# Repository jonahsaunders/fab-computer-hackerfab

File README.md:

# FAB Computer · HackerFab

A reusable power and control backplane with plug-in boards for HackerFab tools.

[Backplane](#backplane) · [Motion controller](#motion-controller) · [Encoder splitter](#encoder-splitter) · [Sputtering cards](#sputtering-cards) · [Plug-in assembly](#plug-in-assembly)

[Manufacturing guide, JLCPCB files, and part alternatives](docs/manufacturing/README.md)

## Boards

### Backplane

[Full-size board render](docs/images/backplane.png) · [L3 inductor close-up](docs/images/backplane-regulator.png)

*KiCad 3D render of the November 10 backplane layout with revised 12 V and 5 V buck regulator placement.*

### Motion controller

### Encoder splitter

### Sputtering cards

[Card details and renders](daughterboards/sputtering/README.md) · [Card validation](daughterboards/sputtering/docs/validation.md)

## Plug-in assembly

*KiCad render with the motion controller in J1 and the encoder splitter in J2.* [Reverse view](daughterboards/micromanipulator/docs/host-adjacent-back.png)

*KiCad render with the pump, gauge and USB card in J1 and the Alicat card in J2.* [Reverse view](daughterboards/sputtering/docs/host-adjacent-back.png)

## Design files

| Board | Purpose | Open in KiCad 10 |
| --- | --- | --- |
| Backplane | RP2350B host, three DIN96 slots, shared power and buses | [Project](hardware/backplane/HackerfabBackplane.kicad_pro) · [Schematics](docs/schematics/README.md) |
| Motion controller | Bare RP2350B; XYZ motion, rotation, heater, vacuum and USB-C; 100 × 60 mm | [Project](daughterboards/micromanipulator/hardware/daughterboard/FabNanoDaughterboard.kicad_pro) · [Schematic](daughterboards/micromanipulator/docs/schematic-review.pdf) |
| Encoder splitter | Existing backplane SPI0 to three original PH6 sensor interfaces; 100 × 26 mm | [Project](daughterboards/micromanipulator/hardware/encoder-backplane/EncoderBackplane.kicad_pro) · [Schematic](daughterboards/micromanipulator/docs/encoder-backplane-schematic.pdf) |
| Sputtering pump + gauge + USB | Pump, gauge and impedance-matcher USB; 100 × 65 mm | [Project](daughterboards/sputtering/hardware/pump-gauge-usb/sputtering-pump-gauge-usb.kicad_pro) · [Schematic](daughterboards/sputtering/docs/sputtering-pump-gauge-usb-schematic.pdf) |
| Sputtering Alicat | Two Alicat flow controllers; 100 × 85 mm | [Project](daughterboards/sputtering/hardware/alicat/sputtering-alicat.kicad_pro) · [Schematic](daughterboards/sputtering/docs/sputtering-alicat-schematic.pdf) |

Clone the entire repository and keep the local libraries together. The motion and encoder cards are four-layer designs with no development modules. The sputtering cards are two-layer designs controlled by the host.

Use host **J1 or J2 for motion**, and another slot for the splitter. **The motion controller owns SPI0; host GPIO16–21 must remain inputs with no pulls.** Other cards must leave SPI0 undriven. See the [bus map and firmware requirements](daughterboards/micromanipulator/docs/backplane-encoder-bus.md).

The motion and encoder cards pass ERC, DRC, connectivity and schematic parity. Physical fit, actual load/thermal measurements, encoder signal integrity and firmware integration remain open. The backplane has its [separate validation record](docs/validation.md). All 5 V loads share the host's **2.5 A power-mux limit**; see [load limits](daughterboards/micromanipulator/docs/load-power-review.md).

[Card details and renders](daughterboards/micromanipulator/README.md) · [Card validation](daughterboards/micromanipulator/docs/validation.md) · [Architecture](docs/architecture.md) · [Connector pinout](docs/connector-pinout.md) · [Contributing](CONTRIBUTING.md)

Backplane sources: **Jonah Saunders**. Project background: **Jonah Saunders and Jacob Rohozen**. [Source history](docs/provenance.md) and [upstream licenses](daughterboards/micromanipulator/licenses/) are retained; no overall project license has been specified.

## Enclosure

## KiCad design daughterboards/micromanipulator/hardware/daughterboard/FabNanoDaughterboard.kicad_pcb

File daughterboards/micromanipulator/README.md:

# Micromanipulator cards

Bare-component adaptation of [MicroManipulatorStepper](https://github.com/hacker-fab/MicroManipulatorStepper) for the FAB Computer backplane. One RP2350B controls XYZ motion, rotation, heater and vacuum. A second, shallow card distributes encoder SPI to the three existing sensor boards. No development boards are used.

| Board | Size | Open in KiCad 10 | Review |
| --- | --- | --- | --- |
| Motion controller | 100 × 60 mm, 4 layers | [Project](hardware/daughterboard/FabNanoDaughterboard.kicad_pro) | [Schematic](docs/schematic-review.pdf), [3D](docs/board-3d.png), [BOM](docs/bom.csv) |
| Encoder splitter | 100 × 26 mm, 4 layers | [Project](hardware/encoder-backplane/EncoderBackplane.kicad_pro) | [Schematic](docs/encoder-backplane-schematic.pdf), [3D](docs/encoder-backplane.png), [BOM](docs/encoder-backplane-bom.csv) |

Keep this folder together: footprints and models resolve locally or through embedded data, with original library names preserved. Standard KiCad symbol libraries are needed for editing. Both boards use **signal / power / ground / signal**, SMD capacitors, edge-accessible connectors, and 0.8 mm bare 5 V/3.3 V probes with nearby grounds. The motion board has 117 fitted components plus four probe pads; the splitter has 11 plus four. Some models are explicitly nominal; see the [model inventory](docs/model-inventory.csv).

## Installation and bus ownership

Place motion in host **J1 or J2**; J3 lacks UART. The encoder card can use any remaining slot. SPI travels through the existing backplane contacts. **Motion owns SPI0; the host must leave GPIO16–21 as inputs with no pulls.** All three SPI0 selects are reserved for these encoders. Other cards must leave this bus undriven. The backplane design is unchanged; no 3.3 V contact was added. Local regulators derive 3.3 V from the existing 5 V rail.

The three PH6 sensor ports preserve their original pin order. The old PH8 cable connection is replaced by the DIN bus; motion GPIO44/45/46 now select the sensors. Rotation encoder J12 remains unchanged. See the [bus/contact map](docs/backplane-encoder-bus.md), [connector table](docs/connectors.csv) and [firmware integration notes](firmware/README.md). The [original 36 × 36 mm splitter](hardware/encoder-splitter/) is retained only as a source reference.

## Review status

Both active boards pass native ERC, DRC, connectivity and schematic parity; all nine schematic pages pass the geometric text/wire audit. The 35 checked direct decoupling paths and all 48 local capacitor ground returns on the motion card remain intact. USB routing now uses two signal vias per connector-to-MCU path (five physical data vias across the reversible branches) with a local ground reference beneath its connector/ESD launch; see the [USB review](docs/usb-routing-review.md). See [validation](docs/validation.md), [routing](docs/layout-front.svg), [power plane](docs/power-plane.svg), [decoupling](docs/decoupling-review.md), and [reverse assembly view](docs/host-adjacent-back.png).

These are development designs. The assembly uses nominal mating-model placement; physical seating, plugs and cable access need verification. Begin encoder SPI at 1 MHz and validate the actual harness before using the original 8 MHz rate. Firmware consolidation is outstanding; configuration headers are included, not binaries.

The host 5 V mux has a **shared 2.5 A limit**. Heater, pump, sensors, host and logic must fit within that total with margin. The source heater estimates 1.4 A; rotation/pump currents remain unspecified in the checked upstream repository. See [load limits](docs/load-power-review.md), [logic supply](docs/power-budget.md), [connector fit](docs/connector-review.md) and [sources/licenses](licenses/). No fabrication release is claimed.

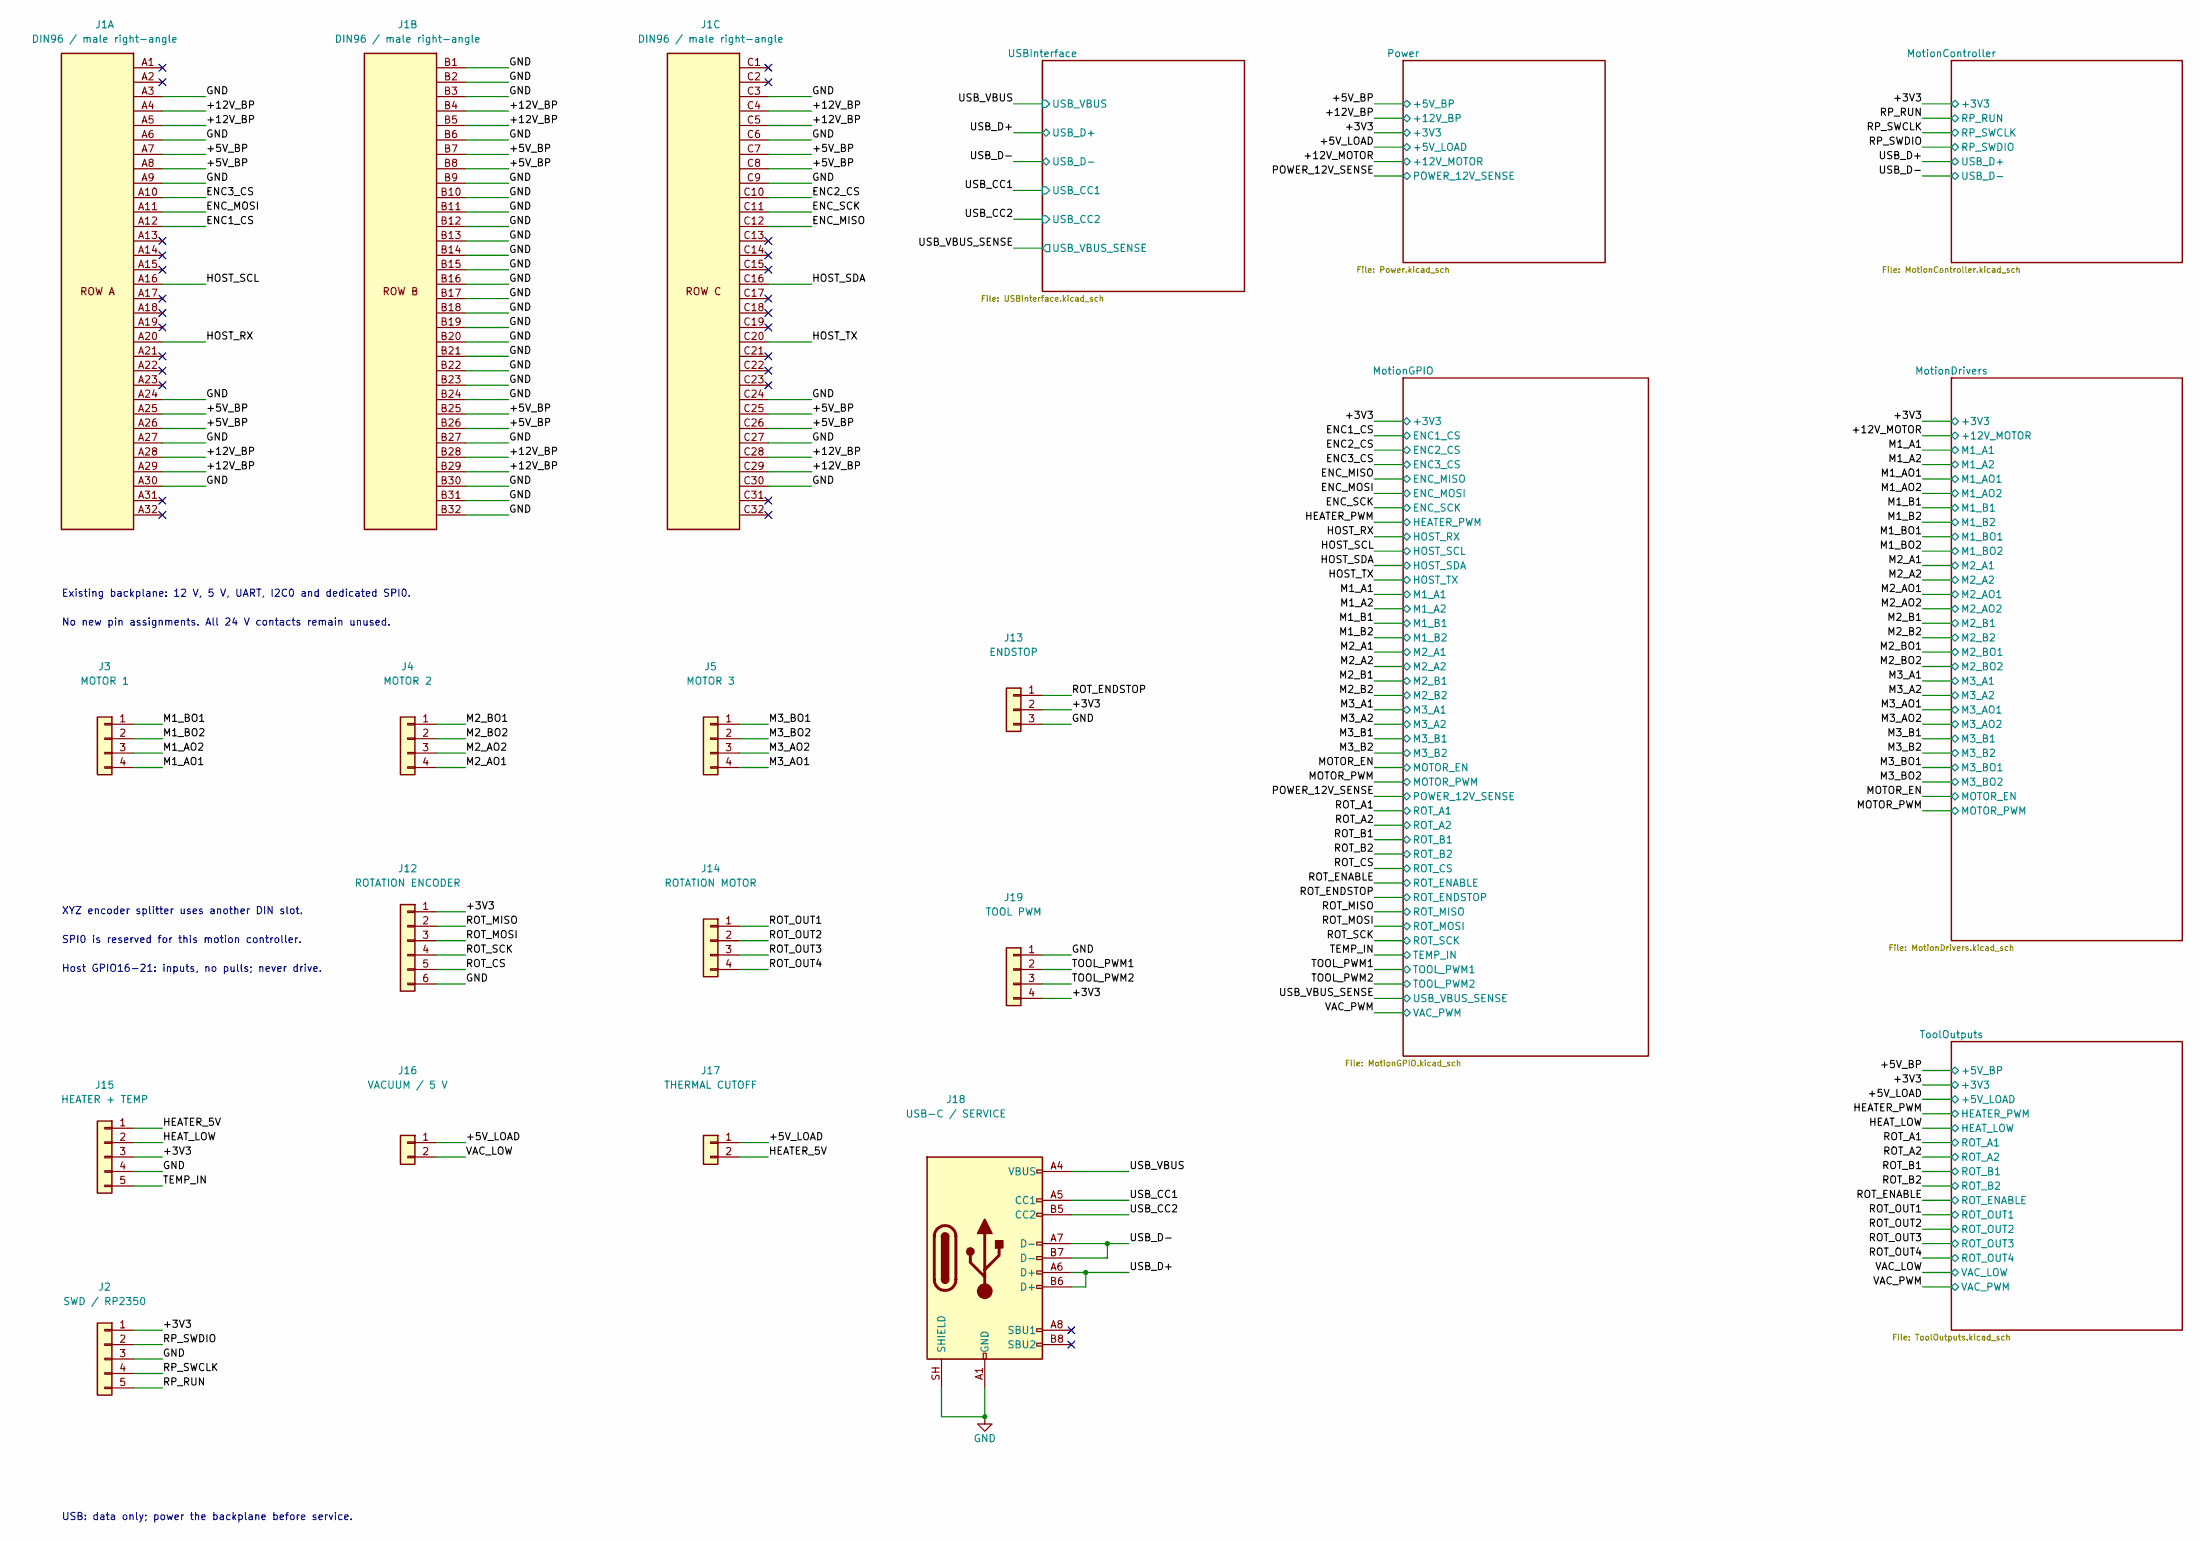
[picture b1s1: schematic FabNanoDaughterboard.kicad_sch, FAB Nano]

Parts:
J1: DIN96 / male right-angle; DIN96_Male_Horizontal; MPN 9001-11961C00A; LCSC C5173361
J2: SWD / RP2350; PinHeader_1x05_P1.27mm_Vertical; MPN PH1.27-01-05PZD; LCSC C41360740
J3: MOTOR 1; JST_PH_B4B-PH-K_1x04_P2.00mm_Vertical; MPN B4B-PH-K-S(LF)(SN); LCSC C131334
J4: MOTOR 2; JST_PH_B4B-PH-K_1x04_P2.00mm_Vertical; MPN B4B-PH-K-S(LF)(SN); LCSC C131334
J5: MOTOR 3; JST_PH_B4B-PH-K_1x04_P2.00mm_Vertical; MPN B4B-PH-K-S(LF)(SN); LCSC C131334
J12: ROTATION ENCODER; PinHeader_1x06_P2.54mm_Vertical; MPN 2.54-1x6PStraight pin; LCSC C37208
J13: ENDSTOP; JST_PH_B3B-PH-K_1x03_P2.00mm_Vertical; MPN B3B-PH-K-S(LF)(SN); LCSC C131339
J14: ROTATION MOTOR; JST_PH_B4B-PH-K_1x04_P2.00mm_Vertical; MPN B4B-PH-K-S(LF)(SN); LCSC C131334
J15: HEATER + TEMP; JST_PH_B5B-PH-K_1x05_P2.00mm_Vertical; MPN B5B-PH-K-S(LF)(SN); LCSC C157993
J16: VACUUM / 5 V; JST_PH_B2B-PH-K_1x02_P2.00mm_Vertical; MPN B2B-PH-K-S(LF)(SN); LCSC C131337
J17: THERMAL CUTOFF; JST_PH_B2B-PH-K_1x02_P2.00mm_Vertical; MPN B2B-PH-K-S(LF)(SN); LCSC C131337
J18: USB-C / SERVICE; USB_C_Receptacle_HRO_TYPE-C-31-M-12; MPN TYPE-C-31-M-12; LCSC C165948
J19: TOOL PWM; PinHeader_1x04_P1.27mm_Vertical; MPN PH1.27-01-04PZD; LCSC C41360739

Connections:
+3V3: J2.1, J12.1, J13.2, J15.3, J19.4; also elsewhere on the board
+5V_BP: J1.A7, J1.A8, J1.A25, J1.A26, J1.B7, J1.B8, J1.B25, J1.B26, J1.C7, J1.C8, J1.C25, J1.C26; also elsewhere on the board
+5V_LOAD: J16.1, J17.1; also elsewhere on the board
+12V_BP: J1.A4, J1.A5, J1.A28, J1.A29, J1.B4, J1.B5, J1.B28, J1.B29, J1.C4, J1.C5, J1.C28, J1.C29; also elsewhere on the board
/ENC1_CS: J1.A12; also elsewhere on the board
/ENC2_CS: J1.C10; also elsewhere on the board
/ENC3_CS: J1.A10; also elsewhere on the board
/ENC_MISO: J1.C12; also elsewhere on the board
/ENC_MOSI: J1.A11; also elsewhere on the board
/ENC_SCK: J1.C11; also elsewhere on the board
/HEATER_5V: J15.1, J17.2
/HEAT_LOW: J15.2; also elsewhere on the board
/HOST_RX: J1.A20; also elsewhere on the board
/HOST_SCL: J1.A16; also elsewhere on the board
/HOST_SDA: J1.C16; also elsewhere on the board
/HOST_TX: J1.C20; also elsewhere on the board
/M1_AO1: J3.4; also elsewhere on the board
/M1_AO2: J3.3; also elsewhere on the board
/M1_BO1: J3.1; also elsewhere on the board
/M1_BO2: J3.2; also elsewhere on the board
/M2_AO1: J4.4; also elsewhere on the board
/M2_AO2: J4.3; also elsewhere on the board
/M2_BO1: J4.1; also elsewhere on the board
/M2_BO2: J4.2; also elsewhere on the board
/M3_AO1: J5.4; also elsewhere on the board
/M3_AO2: J5.3; also elsewhere on the board
/M3_BO1: J5.1; also elsewhere on the board
/M3_BO2: J5.2; also elsewhere on the board
/ROT_CS: J12.5; also elsewhere on the board
/ROT_ENDSTOP: J13.1; also elsewhere on the board
/ROT_MISO: J12.2; also elsewhere on the board
/ROT_MOSI: J12.3; also elsewhere on the board
/ROT_OUT1: J14.1; also elsewhere on the board
/ROT_OUT2: J14.2; also elsewhere on the board
/ROT_OUT3: J14.3; also elsewhere on the board
/ROT_OUT4: J14.4; also elsewhere on the board
/ROT_SCK: J12.4; also elsewhere on the board
/RP_RUN: J2.5; also elsewhere on the board
/RP_SWCLK: J2.4; also elsewhere on the board
/RP_SWDIO: J2.2; also elsewhere on the board
/TEMP_IN: J15.5; also elsewhere on the board
/TOOL_PWM1: J19.2; also elsewhere on the board
/TOOL_PWM2: J19.3; also elsewhere on the board
/USB_CC1: J18.A5 (CC1); also elsewhere on the board
/USB_CC2: J18.B5 (CC2); also elsewhere on the board
/USB_D+: J18.A6 (D+), J18.B6 (D+); also elsewhere on the board
/USB_D-: J18.A7 (D-), J18.B7 (D-); also elsewhere on the board
/USB_VBUS: J18.A4 (VBUS), J18.A9 (VBUS), J18.B4 (VBUS), J18.B9 (VBUS); also elsewhere on the board
/VAC_LOW: J16.2; also elsewhere on the board
GND: J1.A3, J1.A6, J1.A9, J1.A24, J1.A27, J1.A30, J1.B1, J1.B2, J1.B3, J1.B6, J1.B9, J1.B10, J1.B11, J1.B12, J1.B13, J1.B14, J1.B15, J1.B16, J1.B17, J1.B18, J1.B19, J1.B20, J1.B21, J1.B22, J1.B23, J1.B24, J1.B27, J1.B30, J1.B31, J1.B32, J1.C3, J1.C6, J1.C9, J1.C24, J1.C27, J1.C30, J2.3, J12.6, J13.3, J15.4, J18.A1 (GND), J18.A12 (GND), J18.B1 (GND), J18.B12 (GND), J18.SH (SHIELD), J19.1; also elsewhere on the board

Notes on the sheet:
Existing backplane: 12 V, 5 V, UART, I2C0 and dedicated SPI0.
No new pin assignments. All 24 V contacts remain unused.
USB: data only; power the backplane before service.
XYZ encoder splitter uses another DIN slot.
SPI0 is reserved for this motion controller.
Host GPIO16-21: inputs, no pulls; never drive.

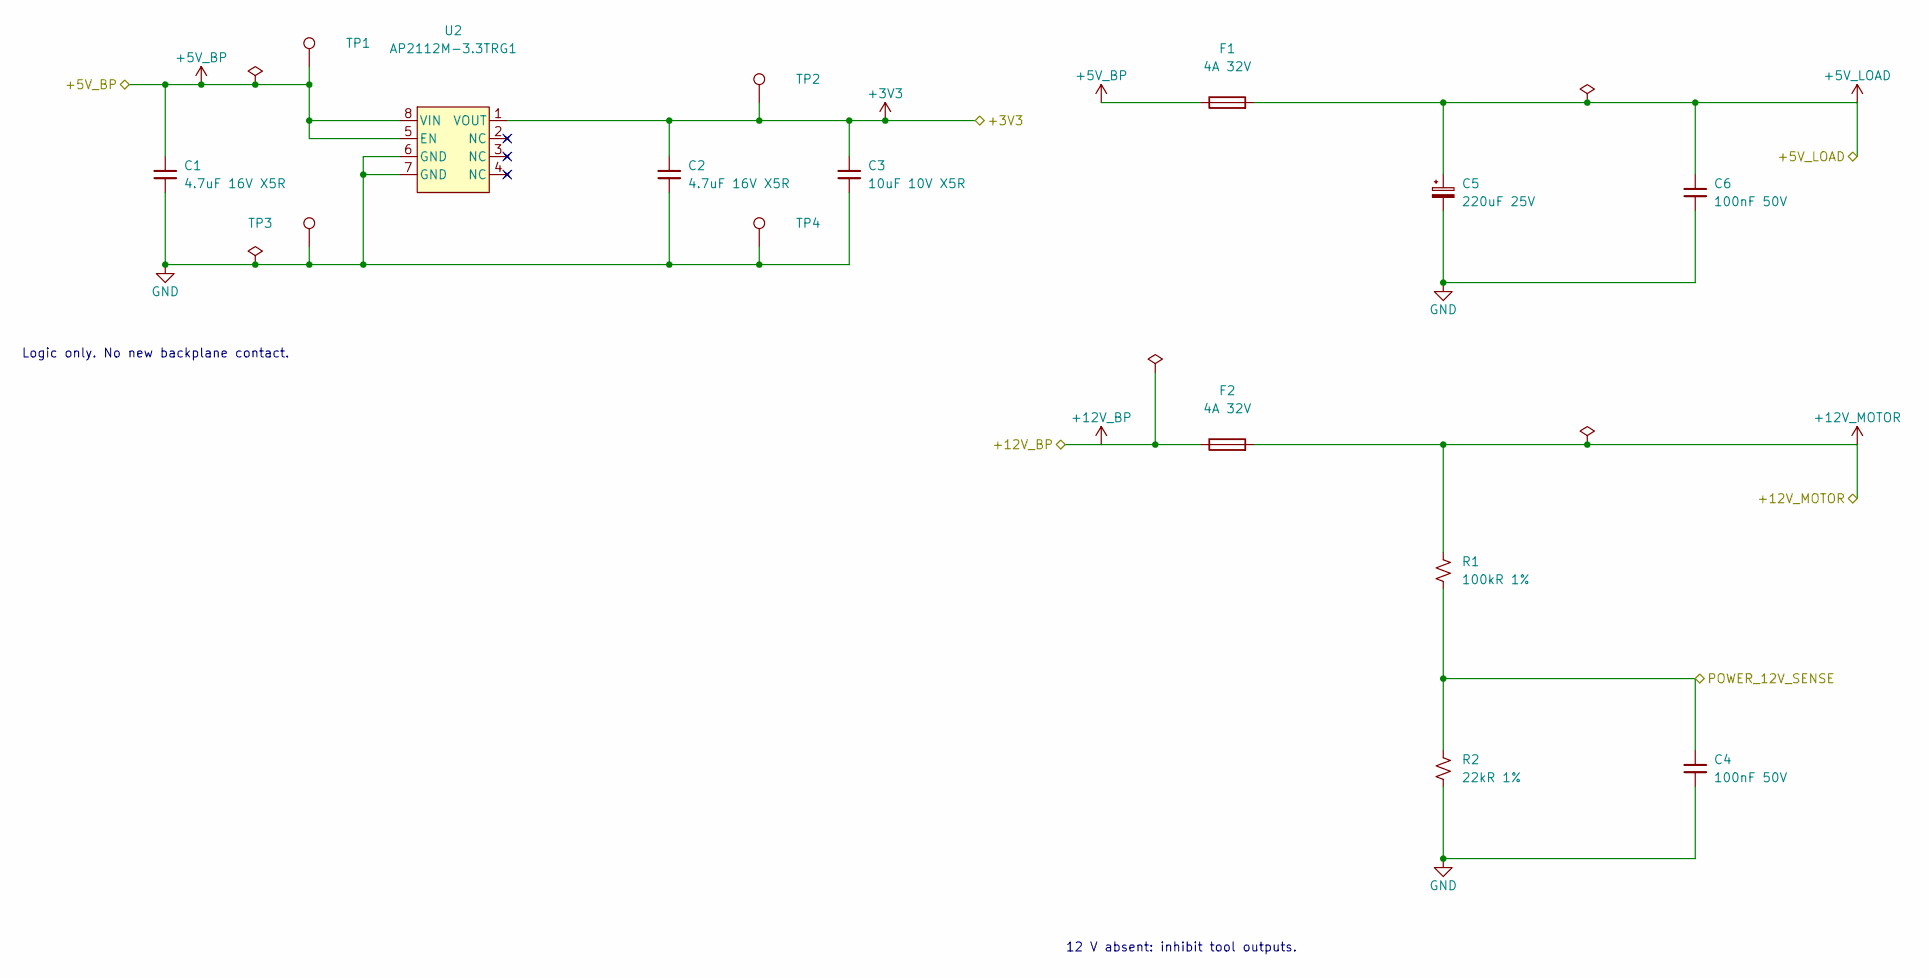
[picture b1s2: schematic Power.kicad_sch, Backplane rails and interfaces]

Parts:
C1, C2: 4.7uF 16V X5R; C_0603_1608Metric; MPN CL10A475KO8NNNC; LCSC C19666
C3: 10uF 10V X5R; C_0603_1608Metric; MPN CL10A106KP8NNNC; LCSC C19702
C4, C6: 100nF 50V; C_0603_1608Metric; MPN CC0603KRX7R9BB104; LCSC C14663
C5: 220uF 25V; CP_Elec_6.3x7.7; MPN 217EC0037; LCSC C42371908
F1, F2: 4A 32V; Fuse_Littelfuse_0466_1206; MPN 0466004.NRHF; LCSC C187596
R1: 100kR 1%; R_0603_1608Metric; MPN 0603WAF1003T5E; LCSC C25803
R2: 22kR 1%; R_0603_1608Metric; MPN 0603WAF2202T5E; LCSC C31850
TP1: 5V; TestPoint_Pad_D0.8mm
TP2: 3V3; TestPoint_Pad_D0.8mm
TP3, TP4: GND; TestPoint_Pad_D0.8mm
U2: AP2112M-3.3TRG1; SOIC-8_3.9x4.9mm_P1.27mm; MPN AP2112M-3.3TRG1; LCSC C5290219

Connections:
+3V3: C2.1, C3.1, TP2.1, U2.1 (VOUT); also elsewhere on the board
+5V_BP: C1.1, F1.1, TP1.1, U2.5 (EN), U2.8 (VIN); also elsewhere on the board
+5V_LOAD: C5.1, C6.1, F1.2; also elsewhere on the board
+12V_BP: F2.1; also elsewhere on the board
+12V_MOTOR: F2.2, R1.1; also elsewhere on the board
/POWER_12V_SENSE: C4.1, R1.2, R2.1; also elsewhere on the board
GND: C1.2, C2.2, C3.2, C4.2, C5.2, C6.2, R2.2, TP3.1, TP4.1, U2.6 (GND), U2.7 (GND); also elsewhere on the board

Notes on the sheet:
Logic only. No new backplane contact.
12 V absent: inhibit tool outputs.

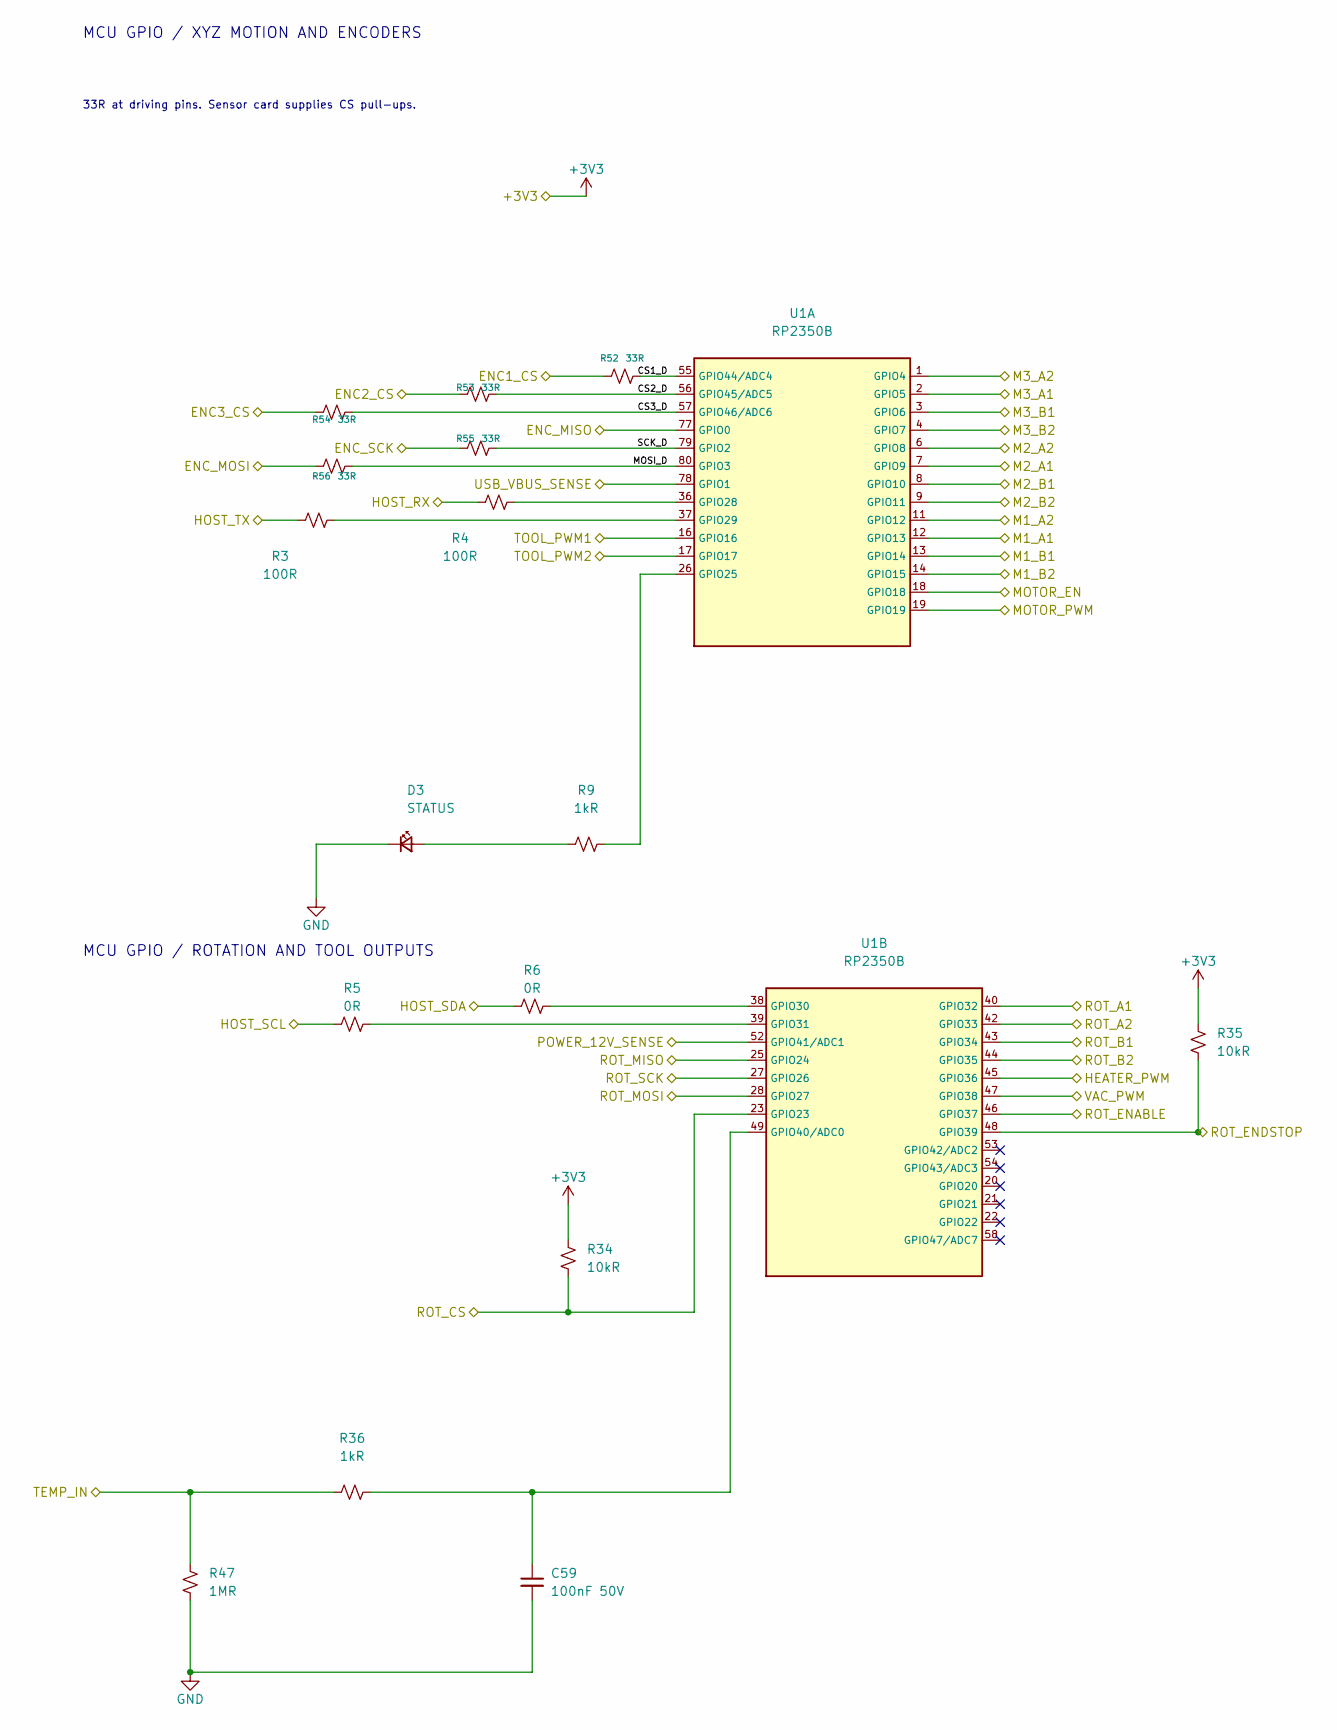
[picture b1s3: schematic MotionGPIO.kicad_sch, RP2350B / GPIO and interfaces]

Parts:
C59: 100nF 50V; C_0603_1608Metric; MPN CC0603KRX7R9BB104; LCSC C14663
D3: STATUS; LED_0603_1608Metric; MPN LTST-C190KGKT; LCSC C125094
R3, R4: 100R; R_0603_1608Metric; MPN 0603WAF1000T5E; LCSC C22775
R5, R6: 0R; R_0603_1608Metric; MPN 0603WAF0000T5E; LCSC C21189
R9, R36: 1kR; R_0603_1608Metric; MPN 0603WAF1001T5E; LCSC C21190
R34, R35: 10kR; R_0603_1608Metric; MPN 0603WAF1002T5E; LCSC C25804
R47: 1MR; R_0603_1608Metric; MPN 0603WAF1004T5E; LCSC C22935
R52, R53, R54, R55, R56: 33R; R_0402_1005Metric; MPN 0402WGF330JTCE; LCSC C25105
U1: RP2350B; QFN-80-1EP_10x10mm_P0.4mm_EP3.4x3.4mm; MPN RP2350B A4; LCSC C9900208890

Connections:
+3V3: R34.1, R35.1; also elsewhere on the board
/ENC1_CS: R52.2; also elsewhere on the board
/ENC2_CS: R53.2; also elsewhere on the board
/ENC3_CS: R54.2; also elsewhere on the board
/ENC_MISO: U1.77 (GPIO0); also elsewhere on the board
/ENC_MOSI: R56.2; also elsewhere on the board
/ENC_SCK: R55.2; also elsewhere on the board
/HEATER_PWM: U1.45 (GPIO36); also elsewhere on the board
/HOST_RX: R4.2; also elsewhere on the board
/HOST_SCL: R5.1; also elsewhere on the board
/HOST_SDA: R6.1; also elsewhere on the board
/HOST_TX: R3.1; also elsewhere on the board
/M1_A1: U1.12 (GPIO13); also elsewhere on the board
/M1_A2: U1.11 (GPIO12); also elsewhere on the board
/M1_B1: U1.13 (GPIO14); also elsewhere on the board
/M1_B2: U1.14 (GPIO15); also elsewhere on the board
/M2_A1: U1.7 (GPIO9); also elsewhere on the board
/M2_A2: U1.6 (GPIO8); also elsewhere on the board
/M2_B1: U1.8 (GPIO10); also elsewhere on the board
/M2_B2: U1.9 (GPIO11); also elsewhere on the board
/M3_A1: U1.2 (GPIO5); also elsewhere on the board
/M3_A2: U1.1 (GPIO4); also elsewhere on the board
/M3_B1: U1.3 (GPIO6); also elsewhere on the board
/M3_B2: U1.4 (GPIO7); also elsewhere on the board
/MOTOR_EN: U1.18 (GPIO18); also elsewhere on the board
/MOTOR_PWM: U1.19 (GPIO19); also elsewhere on the board
/MotionGPIO/CS1_D: R52.1, U1.55 (GPIO44/ADC4)
/MotionGPIO/CS2_D: R53.1, U1.56 (GPIO45/ADC5)
/MotionGPIO/CS3_D: R54.1, U1.57 (GPIO46/ADC6)
/MotionGPIO/MOSI_D: R56.1, U1.80 (GPIO3)
/MotionGPIO/SCK_D: R55.1, U1.79 (GPIO2)
/POWER_12V_SENSE: U1.52 (GPIO41/ADC1); also elsewhere on the board
/ROT_A1: U1.40 (GPIO32); also elsewhere on the board
/ROT_A2: U1.42 (GPIO33); also elsewhere on the board
/ROT_B1: U1.43 (GPIO34); also elsewhere on the board
/ROT_B2: U1.44 (GPIO35); also elsewhere on the board
/ROT_CS: R34.2, U1.23 (GPIO23); also elsewhere on the board
/ROT_ENABLE: U1.46 (GPIO37); also elsewhere on the board
/ROT_ENDSTOP: R35.2, U1.48 (GPIO39); also elsewhere on the board
/ROT_MISO: U1.25 (GPIO24); also elsewhere on the board
/ROT_MOSI: U1.28 (GPIO27); also elsewhere on the board
/ROT_SCK: U1.27 (GPIO26); also elsewhere on the board
/TEMP_IN: R36.1, R47.1; also elsewhere on the board
/TOOL_PWM1: U1.16 (GPIO16); also elsewhere on the board
/TOOL_PWM2: U1.17 (GPIO17); also elsewhere on the board
/USB_VBUS_SENSE: U1.78 (GPIO1); also elsewhere on the board
/VAC_PWM: U1.47 (GPIO38); also elsewhere on the board
GND: C59.2, D3.1 (K), R47.2; also elsewhere on the board
unnamed: D3.2 (A), R9.2
unnamed: R9.1, U1.26 (GPIO25)
unnamed: R4.1, U1.36 (GPIO28)
unnamed: R3.2, U1.37 (GPIO29)
unnamed: R6.2, U1.38 (GPIO30)
unnamed: R5.2, U1.39 (GPIO31)
unnamed: C59.1, R36.2, U1.49 (GPIO40/ADC0)

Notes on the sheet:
MCU GPIO / XYZ MOTION AND ENCODERS
MCU GPIO / ROTATION AND TOOL OUTPUTS
33R at driving pins. Sensor card supplies CS pull-ups.

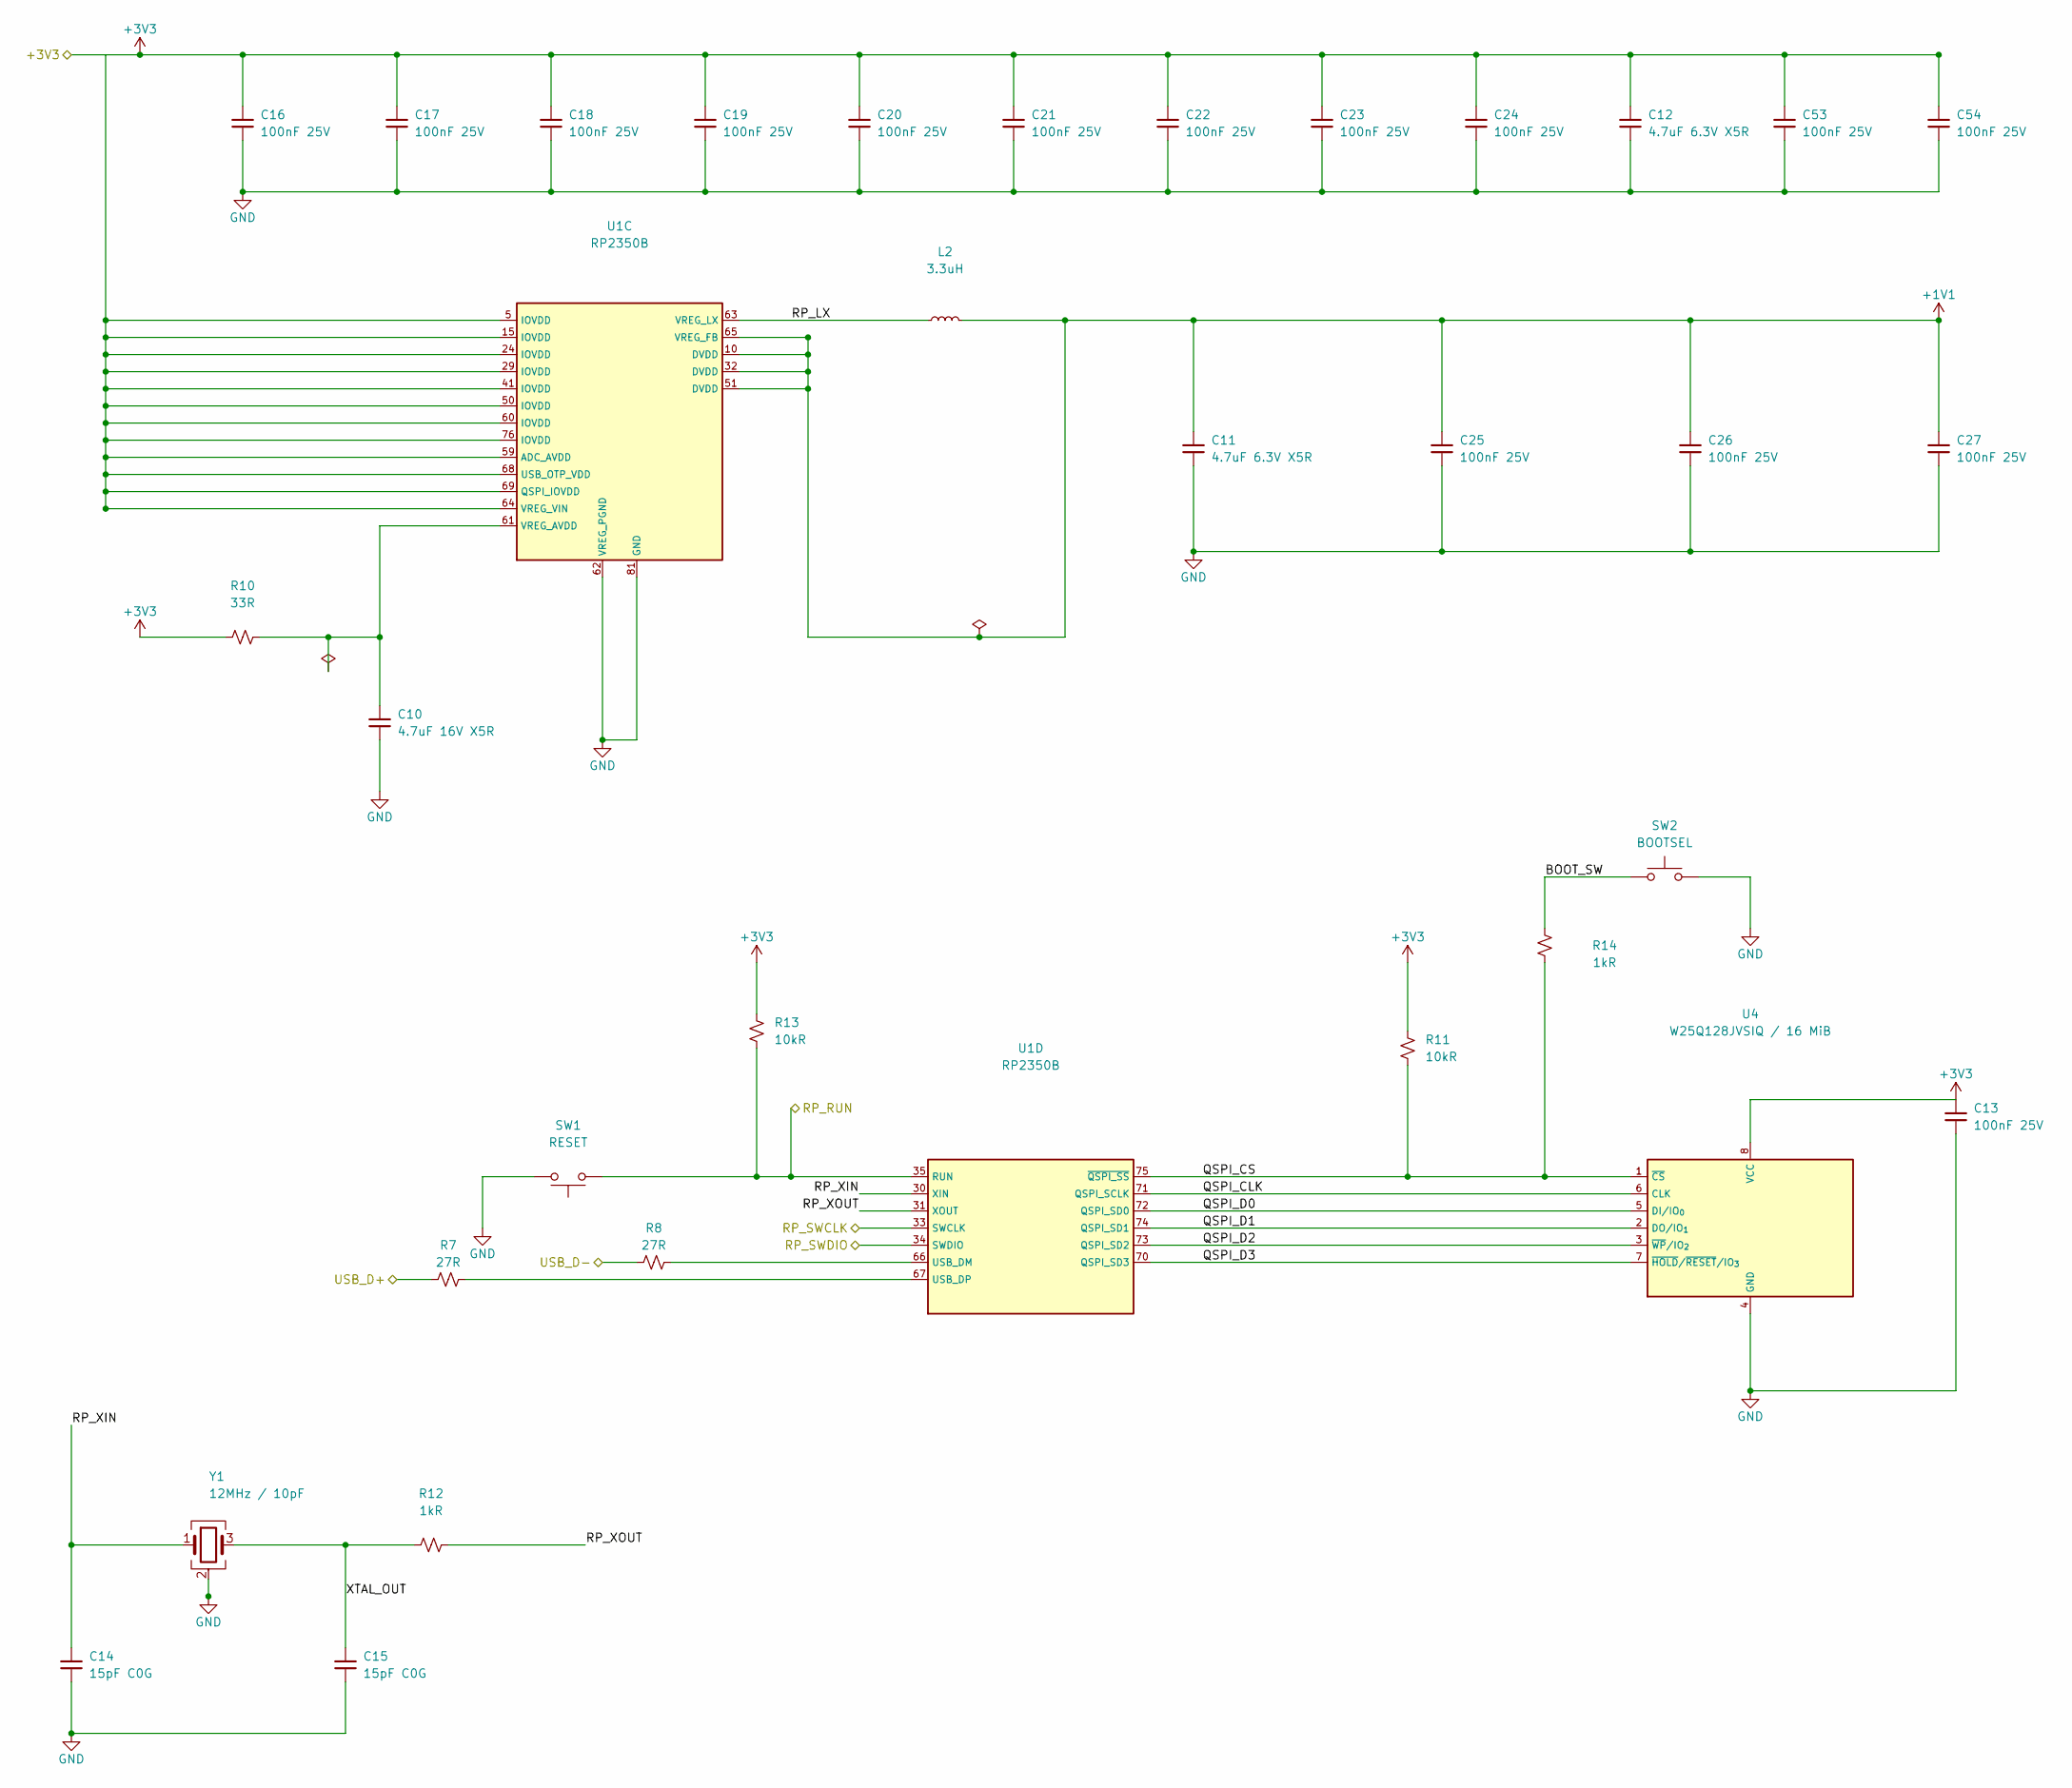
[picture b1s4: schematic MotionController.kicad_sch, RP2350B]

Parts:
C10: 4.7uF 16V X5R; C_0603_1608Metric; MPN CL10A475KO8NNNC; LCSC C19666
C11, C12: 4.7uF 6.3V X5R; C_0402_RP2350_Regulator; MPN GRM155R60J475ME47D; LCSC C82453
C13, C16, C17, C18, C19, C20, C21, C22, C23, C24, C25, C26, C27, C53, C54: 100nF 25V; C_0402_1005Metric; MPN CL05B104KA5NNNC; LCSC C155422
C14, C15: 15pF C0G; C_0402_1005Metric; MPN 0402CG150J500NT; LCSC C1548
L2: 3.3uH; L_Murata_DFE252012F_2.5x2.0mm; MPN DFE252012F-3R3M=P2; LCSC C2041573
R7, R8: 27R; R_0201_Yageo_Reflow; MPN RC0201FR-0727RL; LCSC C273268
R10: 33R; R_0402_1005Metric; MPN 0402WGF330JTCE; LCSC C25105
R11, R13: 10kR; R_0402_1005Metric; MPN 0402WGF1002TCE; LCSC C25744
R12, R14: 1kR; R_0402_1005Metric; MPN 0402WGF1001TCE; LCSC C11702
SW1: RESET; SW_SPST_TL3305A; MPN TL3305AF160QG; LCSC C2886899
SW2: BOOTSEL; SW_SPST_TL3305A; MPN TL3305AF160QG; LCSC C2886899
U1: RP2350B; QFN-80-1EP_10x10mm_P0.4mm_EP3.4x3.4mm; MPN RP2350B A4; LCSC C9900208890
U4: W25Q128JVSIQ / 16 MiB; SOIC-8_5.3x5.3mm_P1.27mm; MPN W25Q128JVSIQ; LCSC C97521
Y1: 12MHz / 10pF; Crystal_SMD_3225-4Pin_3.2x2.5mm; MPN ABM8-272-T3; LCSC C20625731

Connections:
+1V1: C11.1, C25.1, C26.1, C27.1, L2.2, U1.10 (DVDD), U1.32 (DVDD), U1.51 (DVDD), U1.65 (VREG_FB)
+3V3: C12.1, C13.1, C16.1, C17.1, C18.1, C19.1, C20.1, C21.1, C22.1, C23.1, C24.1, C53.1, C54.1, R10.1, R11.1, R13.1, U1.5 (IOVDD), U1.15 (IOVDD), U1.24 (IOVDD), U1.29 (IOVDD), U1.41 (IOVDD), U1.50 (IOVDD), U1.59 (ADC_AVDD), U1.60 (IOVDD), U1.64 (VREG_VIN), U1.68 (USB_OTP_VDD), U1.69 (QSPI_IOVDD), U1.76 (IOVDD), U4.8 (VCC); also elsewhere on the board
/MotionController/BOOT_SW: R14.2, SW2.1
/MotionController/QSPI_CLK: U1.71 (QSPI_SCLK), U4.6 (CLK)
/MotionController/QSPI_CS: R11.2, R14.1, U1.75 (~QSPI_SS), U4.1 (~CS)
/MotionController/QSPI_D0: U1.72 (QSPI_SD0), U4.5 (DI/IO_{0})
/MotionController/QSPI_D1: U1.74 (QSPI_SD1), U4.2 (DO/IO_{1})
/MotionController/QSPI_D2: U1.73 (QSPI_SD2), U4.3 (~WP/IO_{2})
/MotionController/QSPI_D3: U1.70 (QSPI_SD3), U4.7 (~HOLD/~RESET/IO_{3})
/MotionController/RP_LX: L2.1, U1.63 (VREG_LX)
/MotionController/RP_XIN: C14.1, U1.30 (XIN), Y1.1
/MotionController/RP_XOUT: R12.1, U1.31 (XOUT)
/MotionController/XTAL_OUT: C15.1, R12.2, Y1.3
/RP_RUN: R13.2, SW1.1, U1.35 (RUN); also elsewhere on the board
/RP_SWCLK: U1.33 (SWCLK); also elsewhere on the board
/RP_SWDIO: U1.34 (SWDIO); also elsewhere on the board
/USB_D+: R7.2; also elsewhere on the board
/USB_D-: R8.2; also elsewhere on the board
GND: C10.2, C11.2, C12.2, C13.2, C14.2, C15.2, C16.2, C17.2, C18.2, C19.2, C20.2, C21.2, C22.2, C23.2, C24.2, C25.2, C26.2, C27.2, C53.2, C54.2, SW1.2, SW2.2, U1.62 (VREG_PGND), U1.81 (GND), U4.4 (GND), Y1.2 (G), Y1.4 (G); also elsewhere on the board
unnamed: C10.1, R10.2, U1.61 (VREG_AVDD)
unnamed: R8.1, U1.66 (USB_DM)
unnamed: R7.1, U1.67 (USB_DP)
